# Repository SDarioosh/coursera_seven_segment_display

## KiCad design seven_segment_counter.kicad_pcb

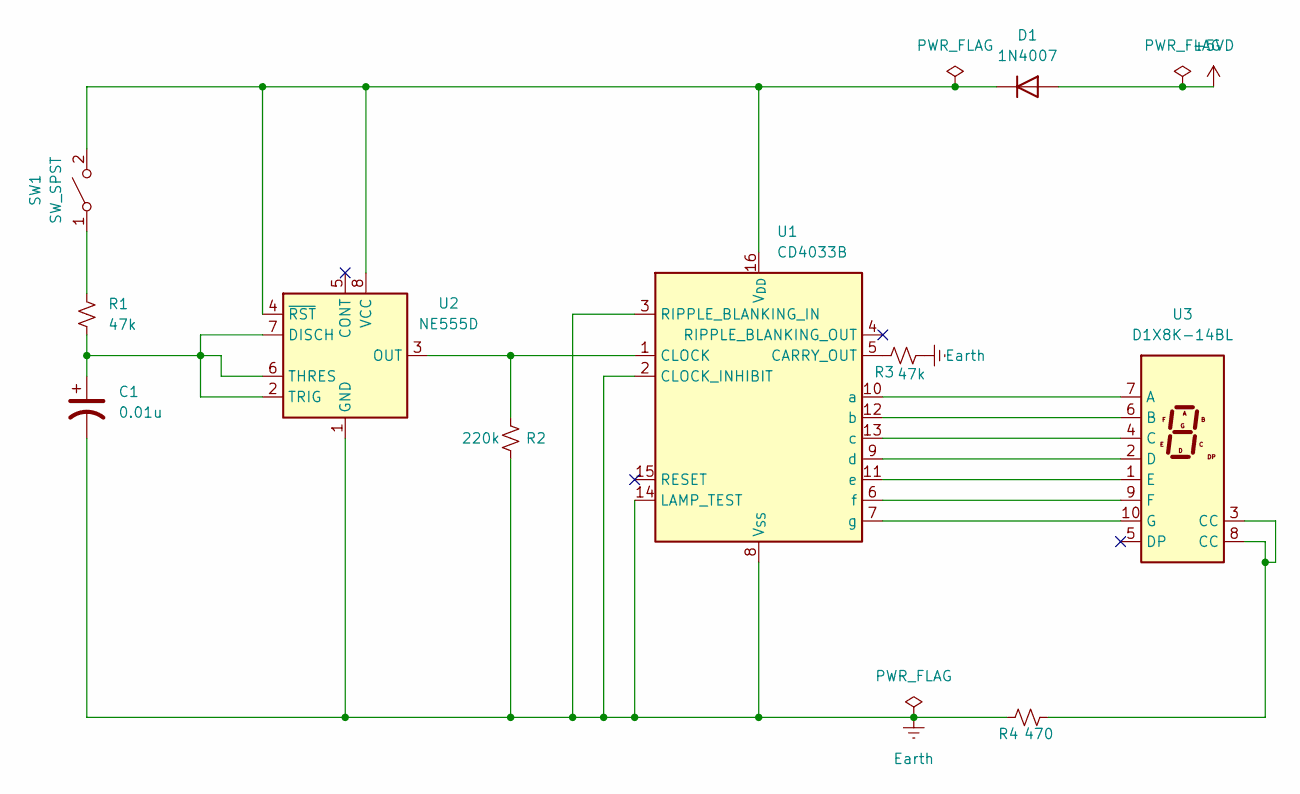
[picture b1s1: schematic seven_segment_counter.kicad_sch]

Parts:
C1: 0.01u; C_0603_1608Metric
D1: 1N4007; D_DO-41_SOD81_P10.16mm_Horizontal
R1, R3: 47k; R_0201_0603Metric
R2: 220k; R_0201_0603Metric
R4: 470; R_0201_0603Metric
SW1: SW_SPST; SW_DIP_SPSTx01_Slide_6.7x4.1mm_W6.73mm_P2.54mm_LowProfile_J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
U1: CD4033B; DIP-16_W7.62mm
U2: NE555D; SOIC-8_3.9x4.9mm_P1.27mm
U3: D1X8K-14BL; D1X8K

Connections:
+5VD: D1.2 (A)
Earth: C1.2, R2.2, R3.2, R4.1, U1.2 (CLOCK_INHIBIT), U1.3 (RIPPLE_BLANKING_IN), U1.8 (V_{SS}), U1.14 (LAMP_TEST), U2.1 (GND)
unnamed: D1.1 (K), SW1.2 (B), U1.16 (V_{DD}), U2.4 (~RST), U2.8 (VCC)
unnamed: R4.2, U3.3 (CC), U3.8 (CC)
unnamed: R1.1, SW1.1 (A)
unnamed: R3.1, U1.5 (CARRY_OUT)
unnamed: R2.1, U1.1 (CLOCK), U2.3 (OUT)
unnamed: U1.10 (a), U3.7 (A)
unnamed: U1.12 (b), U3.6 (B)
unnamed: U1.13 (c), U3.4 (C)
unnamed: U1.9 (d), U3.2 (D)
unnamed: U1.11 (e), U3.1 (E)
unnamed: U1.6 (f), U3.9 (F)
unnamed: U1.7 (g), U3.10 (G)
unnamed: C1.1, R1.2, U2.2 (TRIG), U2.6 (THRES), U2.7 (DISCH)

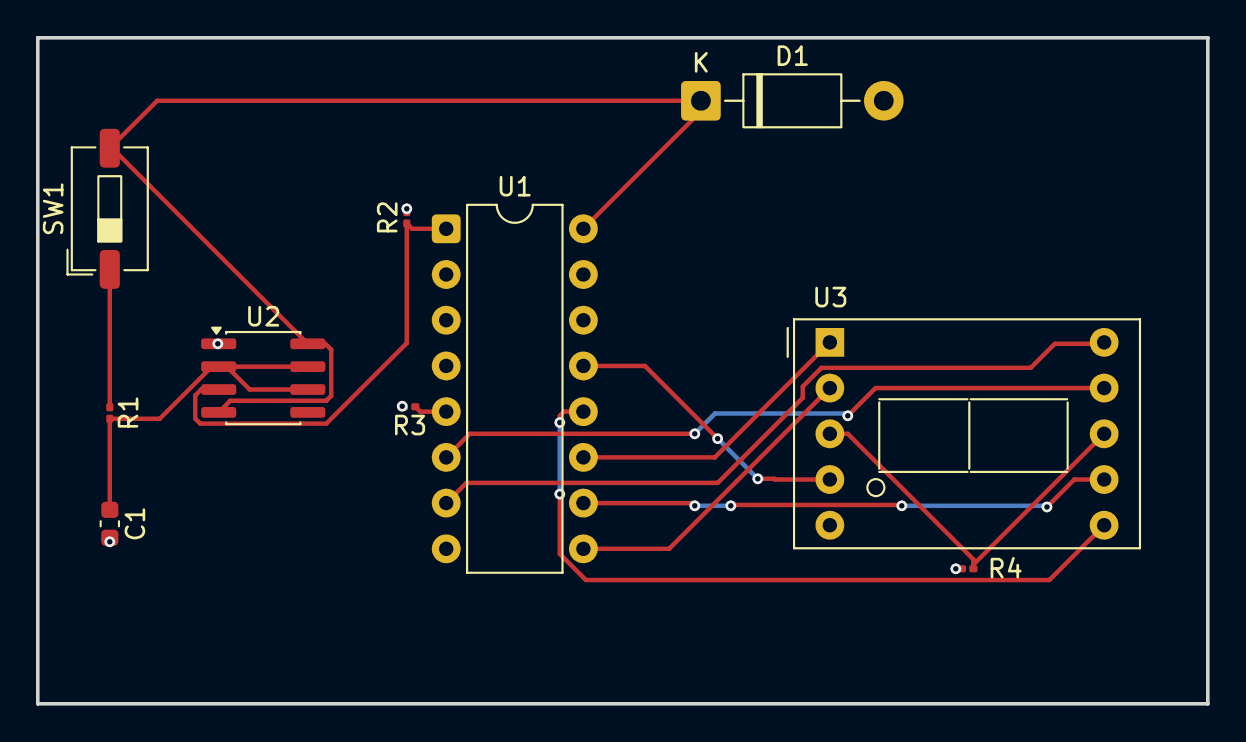
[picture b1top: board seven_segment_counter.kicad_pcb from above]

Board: 2 copper layers, 65.0 x 37.0 mm, 10 parts (0 on the bottom side), 14 nets.
